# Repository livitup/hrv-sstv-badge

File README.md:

# DEFCON SSTV Badge

An open-source SSTV (Slow Scan Television) badge designed for DEFCON and the broader badgelife community. This badge combines amateur radio, digital imaging, and social interaction into a wearable electronic art piece shaped like a Simpsons-style retro TV with rabbit ear antennas.

## Project Overview

The DEFCON SSTV Badge enables users to:
- **Capture photos** with an integrated 2MP OV2640 camera
- **Encode images** into SSTV format with callsign overlay
- **Transmit images** via VHF/UHF radio using the SA818 transceiver
- **Receive SSTV signals** from other badges and stations
- **Store and browse** images on microSD card
- **Interact socially** through visual radio communication

Perfect for ham radio operators, makers, and anyone interested in digital modes and RF experimentation.

## Features

### Hardware Capabilities
- **RP2350B Dual-Core MCU** - QFN-80, 48 GPIOs, dedicated cores for UI and signal processing
- **SA818 VHF/UHF Transceiver** - 1W output on swappable carrier board (see below)
- **OV2640 2MP Camera** - Parallel DVP interface with 15-20 FPS live viewfinder via PIO (module must have its own on-board clock oscillator)
- **2.4" ILI9341 TFT Display** - 320x240 landscape, SPI interface
- **PCM5102A DAC + RP2350 ADC** - I2S DAC for TX audio, internal ADC for RX audio
- **MicroSD Storage** - Standalone SD socket (J10), shared SPI bus with display
- **2000mAh LiPo Battery** - 8-10 hours operation with USB-C charging
- **2x SAO Connectors** - Standard Shitty Add-On expansion ports
- **26x WS2812B LEDs** - Animated blinky chain across rabbit ears and display border

### Radio Features
- **Dual-Band Support** - VHF (134-174 MHz) and UHF (400-480 MHz) via carrier board swap
- **Multiple SSTV Modes** - Martin, Scottie, Robot modes with auto-detection
- **Automatic Operation** - No manual PTT required
- **Airplane Mode** - Physical slide switch to disable RF
- **SMA Antenna Port** - On carrier board, right-angle connector with antenna pointing up

### User Interface
- **5-Way D-Pad** - Navigation, menu selection, and photo capture (center button doubles as shutter)
- **Airplane Mode Switch** - Slide switch for RF enable/disable
- **PWR LED** - Traditional RGB LED for battery and system status
- **Blinky LEDs** - 26x WS2812B chain with animated TX/RX/idle patterns
- **Customizable Settings** - Callsign, frequency, SSTV mode, and more

## SA818 Carrier Board System

The SA818 transceiver has castellated pads (4.45mm pitch) that are incompatible with user-swappable sockets. Instead of mounting the SA818 directly on the main badge, the design uses a full-width carrier board system.

### How It Works

The carrier board is a separate PCB (full badge width, ~120mm) that overlays the top portion of the main badge. The SA818 module, SMA connector, and antenna are ALL on the carrier board -- the main badge has zero RF traces.

**Mounting:** 4-point connection via 2x 1x8 signal headers (bottom edge) + 2x 1x3 mechanical headers (top corners, grounded for RF shielding).

**Band detection:** Each carrier has an ID resistor (0 ohm for VHF, DNP for UHF) read by the RP2350B on startup. The firmware automatically detects which carrier is installed and configures frequency limits accordingly. No DIP switches or manual configuration needed.

### Carrier Variants

- **SA818-V Carrier** - VHF (134-174 MHz) with matched VHF stubby antenna
- **SA818-U Carrier** - UHF (400-480 MHz) with matched UHF stubby antenna

### Swapping Carriers

1. Power down the badge
2. Unplug the current carrier board from the headers
3. Plug in the replacement carrier (VHF or UHF)
4. Power on -- firmware auto-detects the band and configures itself

Each carrier includes a band-matched stubby antenna, so users do not need to source separate antennas.

### Design Benefits

- Main badge PCB has no RF routing, simplifying layout and potentially enabling 2-layer PCB
- Carrier board has proper 50-ohm microstrip trace from SA818 to SMA
- Ground stitching around RF trace on carrier for shielding
- SA818 is factory-assembled onto carrier (castellated module, not socketable)

## Power System

The SA818 draws up to 1.7A during TX, which would overwhelm a standard 3.3V regulator. The power system separates the radio from the digital rail:

```
LiPo (3.0-4.2V) --+---> TPS63001 (buck-boost) ---> 3.3V Rail (RP2350B, display, camera, etc.)
                   |
                   +---> TPS22919 (load switch) ---> SA818 (3.5-5.5V direct from LiPo)
```

- **TPS63001**: Buck-boost regulator, 3.3V output, handles full LiPo voltage range (3.0-4.2V)
- **TPS22919**: Load switch controls SA818 power (enables airplane mode and sleep)
- **MCP73871**: Battery charging controller with USB-C input
- **LC709203F**: Battery fuel gauge (I2C)

## Amateur Radio License Verification System

To comply with FCC Part 97 regulations, the badge includes a software-based license verification system.

### Operating Modes

- **Receive-Only Mode**: Default for unlicensed users. Can receive and decode SSTV images but cannot transmit.
- **Licensed Mode**: Full TX/RX for verified amateur radio operators.

### Verification Process

During initial setup, users enter their amateur radio callsign. The badge generates a unique unlock code from the callsign and the device's hardware serial number using SHA-256 hashing. This ensures each unlock code is specific to one badge-callsign combination, preventing casual code sharing between devices.

Licensed operators get full transmit capability with automatic callsign overlay on transmitted images (FCC requirement). Unlicensed users can still receive and view SSTV images -- all reception features work normally.

This system encourages proper amateur radio operation. It is not intended as absolute copy protection.

## Project Status

**Current Phase: PCB layout complete — pre-fabrication checks**

| Milestone | Status |
|-----------|--------|
| System architecture and block diagram | Complete |
| Schematic design (all sheets) | Complete, ERC clean |
| KiCad schematic entry | Complete (all sheets) |
| SA818 carrier board PCBs (VHF + UHF) | Complete, including harmonic low-pass filters |
| Bill of materials and sourcing | Complete |
| Main badge PCB layout | Complete (routed) |
| Firmware development | Not started |
| Prototype assembly and testing | Pending PCB fabrication |

## Repository Structure

```
hrv-sstv-badge/
├── CLAUDE.md                       # AI context file (project specs)
├── CMakeLists.txt                  # Build system
├── CONTRIBUTING.md                 # Contribution guidelines
├── LICENSE                         # MIT license
├── README.md                       # This file
├── docs/                           # Documentation
│   ├── block-diagram.png           # System overview diagram
│   ├── electrical-design.md        # Circuit schematics and component specs
│   ├── firmware-architecture.md    # Detailed software design
│   ├── bom.md                      # Bill of materials with costs
│   ├── bom-raw.md                  # Raw BOM data
│   ├── project-status.md           # Design status tracker
│   └── engineers-notebook/         # Design decisions and rationale
├── firmware/                       # RP2350B embedded firmware (not yet started)
├── hardware/                       # KiCad PCB design files
│   ├── main_badge/                 # Main badge KiCad project
│   ├── sa818-v-carrier/            # VHF carrier board KiCad project
│   ├── sa818-u-carrier/            # UHF carrier board KiCad project
│   ├── footprints.pretty/          # Custom KiCad footprints
│   ├── symbols/                    # Custom KiCad symbols
│   ├── pcb-design.md               # PCB layout guidelines
│   └── README.md                   # Hardware design notes
├── mechanical/                     # Badge accessories and mounting
└── src/                            # Source scaffolding
```

## Technical Specifications

| Parameter | Specification |
|-----------|---------------|
| **MCU** | Raspberry Pi RP2350B (QFN-80), Dual ARM Cortex-M33 |
| **Radio** | SA818 VHF/UHF on carrier board, 1W output |
| **Frequency Range** | VHF: 134-174 MHz, UHF: 400-480 MHz |
| **Camera** | OV2640, 2MP, parallel DVP (8-bit), QVGA for SSTV |
| **Display** | 2.4" ILI9341 TFT LCD, 320x240 landscape, SPI |
| **Audio TX** | PCM5102A DAC via I2S |
| **Audio RX** | RP2350B internal ADC with anti-alias filter |
| **Storage** | MicroSD via standalone SD socket J10 (shared SPI bus) |
| **Battery** | 2000mAh LiPo, USB-C charging (MCP73871) |
| **Regulator** | TPS63001 buck-boost, 3.3V output |
| **Operating Time** | 8-10 hours typical use |
| **LEDs** | 26x WS2812B (10x 5050 on the two plug-in ears, 16x 2020 on border) + RGB PWR LED |
| **Expansion** | 2x SAO (Shitty Add-On) connectors |
| **Dimensions** | ~120mm x 120mm body, ~199mm total height with ears and feet |
| **Form Factor** | Retro TV shape with plug-in, replaceable rabbit ear antennas; wearable badge (no enclosure) |

## Software Architecture

The firmware uses a bare-metal dual-core design on the RP2350B for deterministic SSTV timing:

- **Core 0**: User interface, file system, system management, display updates
- **Core 1**: SSTV encoding/decoding, audio DSP, camera control, radio management

PIO state machines handle hardware-timed signals (camera capture, WS2812B data, audio clocking). DMA transfers move data without CPU intervention. No RTOS -- bare metal for microsecond-precision SSTV timing.

### Development Environment
- **Language**: C11 (ISO/IEC 9899:2011)
- **Compiler**: GCC ARM Embedded (arm-none-eabi-gcc)
- **Build System**: CMake with Raspberry Pi Pico SDK
- **Debugger**: OpenOCD + GDB via SWD (Tag-Connect)

## Assembly Model

This badge uses a production kit approach:

- **Factory-assembled**: All SMD components on main badge, SA818 onto carrier boards
- **User-assembled at conference**: Through-hole parts (switches, connectors, pin headers)
- **User-configured**: Plug in VHF or UHF carrier board, insert battery, insert SD card

## Getting Started

### Prerequisites
- **Amateur Radio License** - Required for transmit operation (receive works without)
- **Basic Soldering Skills** - Through-hole soldering for final assembly

### Firmware Installation
1. Download the latest firmware release
2. Connect via USB-C while holding BOOTSEL
3. Copy the UF2 file to the mounted drive
4. Configure callsign, frequency, and SSTV mode

### Build from Source
```bash
mkdir build && cd build
cmake .. -DCMAKE_BUILD_TYPE=Debug
make -j4

# Flash via UF2 bootloader
cp defcon_sstv_badge.uf2 /Volumes/RPI-RP2/

# Or flash via SWD
openocd -f interface/cmsis-dap.cfg -f target/rp2350.cfg
```

## Badgelife Integration

- **SAO Compatibility** - 2x standard Shitty Add-On connectors (I2C + 2 GPIOs each)
- **Badge-to-Badge Communication** - SSTV image exchange over the air
- **Retro TV Aesthetic** - PCB shaped like a classic TV with rabbit ear antennas
- **Animated LEDs** - 26 WS2812B LEDs with TX/RX/idle animations across ears and display border
- **Open Source** - Hardware and software fully open for hacking and modification

## Legal and Compliance

### Amateur Radio Requirements
- Valid amateur radio license required for transmit operation
- Operate only within licensed frequency allocations
- Follow local RF exposure and power limitations
- Respect band plans and operating procedures

### Regulatory
- FCC Part 97 (United States)
- IC RSS (Canada)
- CE marking (Europe)
- Consult local regulations for other countries

### Safety
- RF radiation exposure -- use appropriate antenna and power levels
- LiPo battery safety -- follow proper charging and storage procedures
- ESD precautions during assembly

## Contributing

Contributions from the badgelife and amateur radio communities are welcome.

### How to Contribute
- **Report Issues** - Found a bug? Open a GitHub issue
- **Submit Pull Requests** - Code improvements, documentation fixes
- **Share Ideas** - Feature requests and enhancement suggestions
- **Test Hardware** - Help validate designs and assembly procedures

### Development Areas
- **Hardware**: PCB layout, carrier board design
- **Firmware**: SSTV algorithms, UI, power management
- **Documentation**: Assembly guides, user manuals, tutorials

## License

- **Hardware**: [CERN-OHL-S v2](https://cern-ohl.web.cern.ch/)
- **Software**: [MIT License](LICENSE)
- **Documentation**: [CC BY-SA 4.0](https://creativecommons.org/licenses/by-sa/4.0/)

## Support and Community

- **Documentation** - See the `docs/` directory
- **Issues** - Open a GitHub issue for bugs or questions
- **Discussions** - Use GitHub Discussions for general topics
- **DEFCON** - Hardware Hacking Village and Ham Radio Village

---

**Made for the badgelife and amateur radio communities. See you at DEFCON!**

**73s!**

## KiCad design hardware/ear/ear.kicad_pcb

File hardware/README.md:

# DEFCON SSTV Badge — Hardware Design

This directory contains all KiCad design files for the DEFCON SSTV Badge.

## Directory Structure

```
hardware/
├── main_badge/                    # Main badge KiCad project
│   ├── defcon-sstv-badge.kicad_pro    # Project file
│   ├── defcon-sstv-badge.kicad_sch    # Top-level schematic
│   ├── defcon-sstv-badge.kicad_pcb    # PCB layout (in progress)
│   ├── power.kicad_sch                # Power: TPS63001, TPS22919, MCP73871, LC709203F
│   ├── audio.kicad_sch                # Audio: PCM5102A DAC, TX/RX filters
│   ├── camera-display.kicad_sch       # Display (ILI9341) + Camera (OV2640)
│   ├── mcu.kicad_sch                  # RP2350B, crystal, flash, USB-C
│   ├── switches.kicad_sch             # D-pad, airplane switch, PWR LED, WS2812B chain
│   └── connectors.kicad_sch           # SAO×2, carrier headers, SD card, Tag-Connect
├── sa818-v-carrier/               # VHF carrier board (134-174 MHz)
│   ├── sa818-v-carrier.kicad_pro
│   ├── sa818-v-carrier.kicad_sch
│   └── sa818-v-carrier.kicad_pcb      # PCB layout complete
├── sa818-u-carrier/               # UHF carrier board (400-480 MHz)
│   ├── sa818-u-carrier.kicad_pro
│   ├── sa818-u-carrier.kicad_sch
│   └── sa818-u-carrier.kicad_pcb      # PCB layout complete
├── ear/                           # Plug-in rabbit ear LED board (one design, used twice)
│   ├── ear.kicad_pro
│   ├── ear.kicad_sch
│   └── ear.kicad_pcb                  # PCB layout complete
├── symbols/                       # Custom KiCad symbol libraries
├── footprints.pretty/             # Custom KiCad footprint libraries
├── fp-lib-table                   # Footprint library table
├── sym-lib-table                  # Symbol library table
├── pcb-design.md                  # PCB outline, dimensions, and layout zones
└── README.md                      # This file
```

## Design Overview

### Main Badge
- **PCB shape**: Simpsons-style retro TV with stubby feet; the rabbit ear antennas are two plug-in boards (`ear/`)
- **Body dimensions**: 120mm × 120mm
- **Total height**: ~199mm with ears plugged in (main board alone 139mm)
- **Layer count**: Targeting 4-layer (signal/ground/power/signal)
- **Thickness**: 1.6mm standard FR4
- **Soldermask**: Purple with white silkscreen (Simpsons TV aesthetic)

### Rabbit Ears
- **One board, used twice**: 15 × 95.5mm, 2-layer, five WS2812B LEDs and a 2×3 header
- Plugs into sockets J24/J25 on the back of the main badge; replaceable
- See `docs/engineers-notebook/plug-in-ears.md`

### Carrier Boards
- **Size**: Full badge width (~120mm), overlays top of main badge
- **Purpose**: SA818 module + SMA connector + antenna — all RF on carrier, none on main badge
- **Variants**: VHF (SA818-V) and UHF (SA818-U), identical PCB with different module population
- **PCB layout**: Complete for both variants

### Key Design Decisions
- **No RF on main badge** — all RF routing is on the carrier board
- **Carrier is front-mounted** — overlays the top portion of the main badge, top edges flush
- **4-point mounting** — 2× 1×8 signal headers + 2× 1×3 mechanical headers (GND for RF shielding)
- **Band auto-detect** — carrier ID resistor (0Ω to GND = VHF, 10kΩ pull-up = UHF) read by firmware on startup

## KiCad Version

This project uses **KiCad 9**. Custom symbols and footprints are included in the repository.

## Schematic Status

All schematic sheets are complete and ERC clean:
- Power, Audio, Display/Camera, MCU, Switches, Connectors (main badge)
- SA818-V Carrier, SA818-U Carrier

## PCB Layout Status

- **Carrier boards**: Complete (VHF and UHF), including the harmonic low-pass filter; headers mount on the back
- **Main badge**: Routing complete

## Related Documentation

- [PCB Design](pcb-design.md) — Board outline, dimensions, component placement zones
- [Electrical Design](../docs/electrical-design.md) — Circuit schematics and component specs
- [BOM](../docs/bom.md) — Bill of materials with costs and sourcing
- [Project Status](../docs/project-status.md) — Design and implementation tracker

---

*73 de HRV*

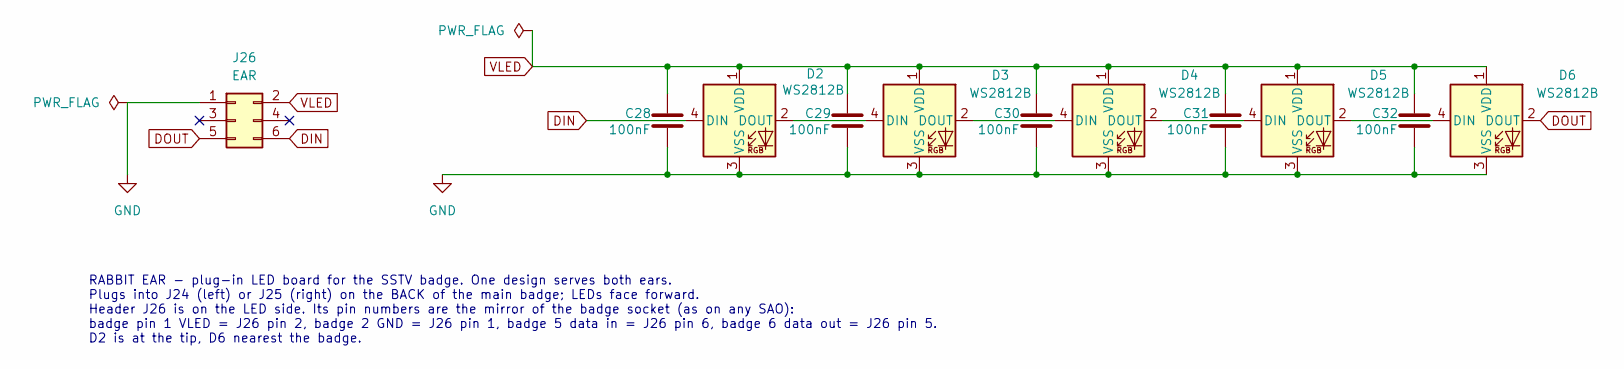
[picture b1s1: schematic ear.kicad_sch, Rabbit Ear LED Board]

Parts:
C28, C29, C30, C31, C32: 100nF; C_0402_1005Metric
D2, D3, D4, D5, D6: WS2812B; LED_WS2812B_PLCC4_5.0x5.0mm_P3.2mm
J26: EAR; PinHeader_2x03_P2.54mm_Vertical

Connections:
DIN: D2.4 (DIN), J26.6
DOUT: D6.2 (DOUT), J26.5
GND: C28.2, C29.2, C30.2, C31.2, C32.2, D2.3 (VSS), D3.3 (VSS), D4.3 (VSS), D5.3 (VSS), D6.3 (VSS), J26.1
unnamed: D2.2 (DOUT), D3.4 (DIN)
unnamed: D3.2 (DOUT), D4.4 (DIN)
unnamed: D4.2 (DOUT), D5.4 (DIN)
unnamed: D5.2 (DOUT), D6.4 (DIN)
VLED: C28.1, C29.1, C30.1, C31.1, C32.1, D2.1 (VDD), D3.1 (VDD), D4.1 (VDD), D5.1 (VDD), D6.1 (VDD), J26.2

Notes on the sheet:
RABBIT EAR - plug-in LED board for the SSTV badge. One design serves both ears. Plugs into J24 (left) or J25 (right) on the BACK of the main badge; LEDs face forward. Header J26 is on the LED side. Its pin numbers are the mirror of the badge socket (as on any SAO): badge pin 1 VLED = J26 pin 2, bad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

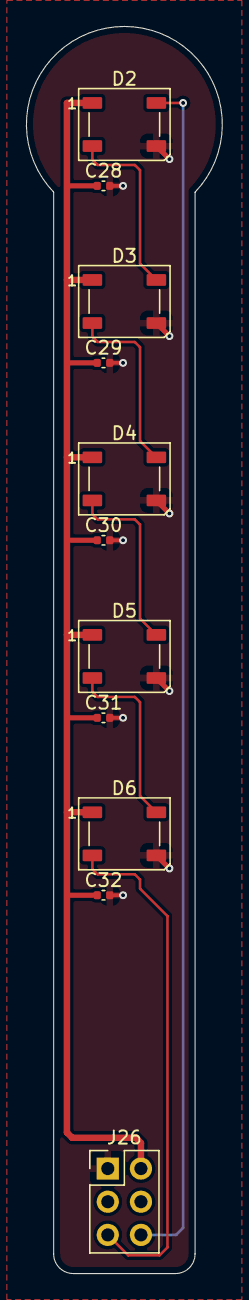
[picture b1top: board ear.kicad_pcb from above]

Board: 2 copper layers, 15.0 x 95.5 mm, 11 parts (0 on the bottom side), 8 nets.

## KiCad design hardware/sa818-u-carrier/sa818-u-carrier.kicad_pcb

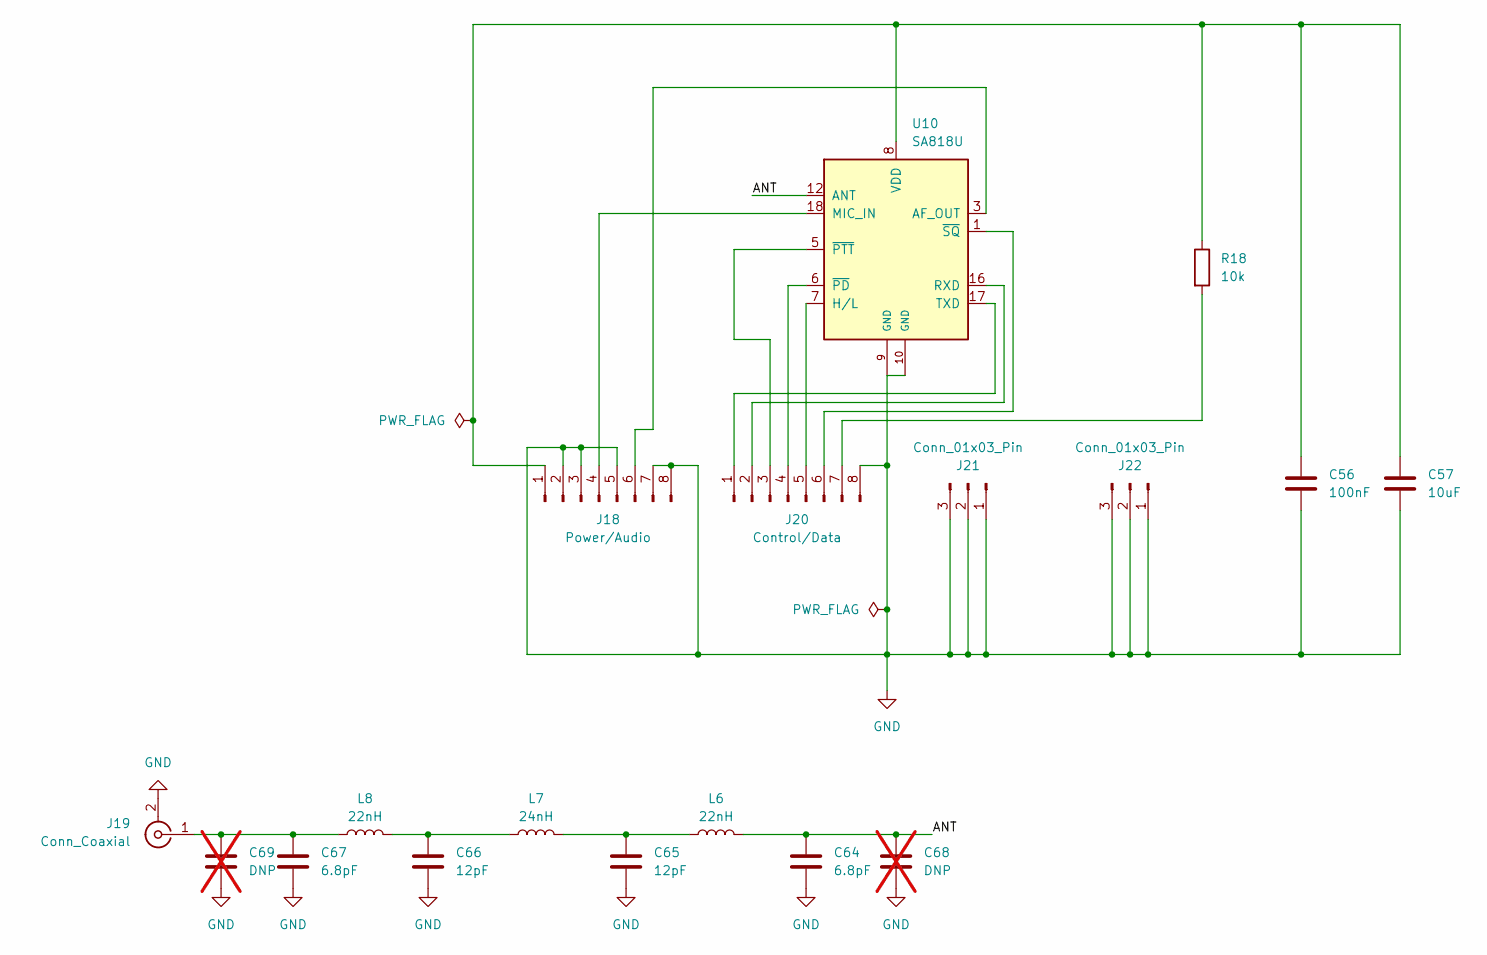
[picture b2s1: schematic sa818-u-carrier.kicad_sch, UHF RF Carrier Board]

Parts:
C56: 100nF; C_0402_1005Metric
C57: 10uF; C_0603_1608Metric
C64, C67: 6.8pF; C_0402_1005Metric
C65, C66: 12pF; C_0402_1005Metric
C68, C69: DNP; C_0402_1005Metric; not fitted
J18: Power/Audio; PinHeader_1x08_P2.54mm_Vertical
J19: Conn_Coaxial; SMA_Amphenol_132289_EdgeMount
J20: Control/Data; PinHeader_1x08_P2.54mm_Vertical
J21, J22: Conn_01x03_Pin; PinHeader_1x03_P2.54mm_Vertical
L6, L8: 22nH; L_0603HP
L7: 24nH; L_0603HP
R18: 10k; R_0402_1005Metric
U10: SA818U; VHF_UHF_Module_generic

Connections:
/ANT: C64.2, C68.1, L6.2, U10.12 (ANT)
GND: C56.2, C57.2, C64.1, C65.1, C66.2, C67.2, C68.2, C69.2, J18.2, J18.3, J18.5, J18.7, J18.8, J19.2 (Ext), J20.8, J21.1, J21.2, J21.3, J22.1, J22.2, J22.3, U10.9 (GND), U10.10 (GND)
unnamed: C65.2, L6.1, L7.2
unnamed: C66.1, L7.1, L8.2
unnamed: C56.1, C57.1, J18.1, R18.1, U10.8 (VDD)
unnamed: J18.4, U10.18 (MIC_IN)
unnamed: J18.6, U10.3 (AF_OUT)
unnamed: C67.1, C69.1, J19.1 (In), L8.1
unnamed: J20.1, U10.17 (TXD)
unnamed: J20.2, U10.16 (RXD)
unnamed: J20.3, U10.5 (~PTT)
unnamed: J20.4, U10.6 (~PD)
unnamed: J20.5, U10.7 (H/L)
unnamed: J20.6, U10.1 (~SQ)
unnamed: J20.7, R18.2

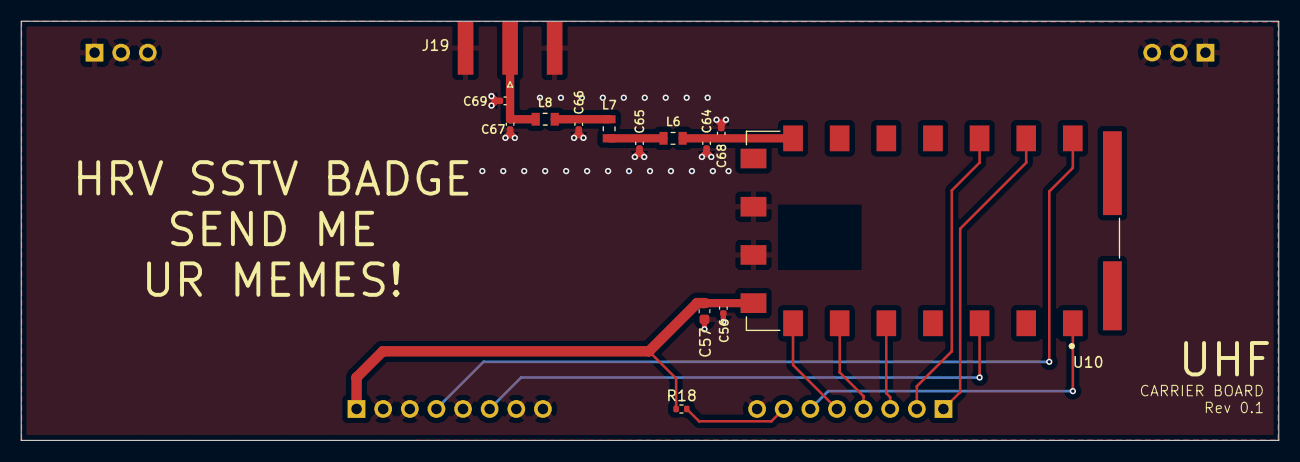
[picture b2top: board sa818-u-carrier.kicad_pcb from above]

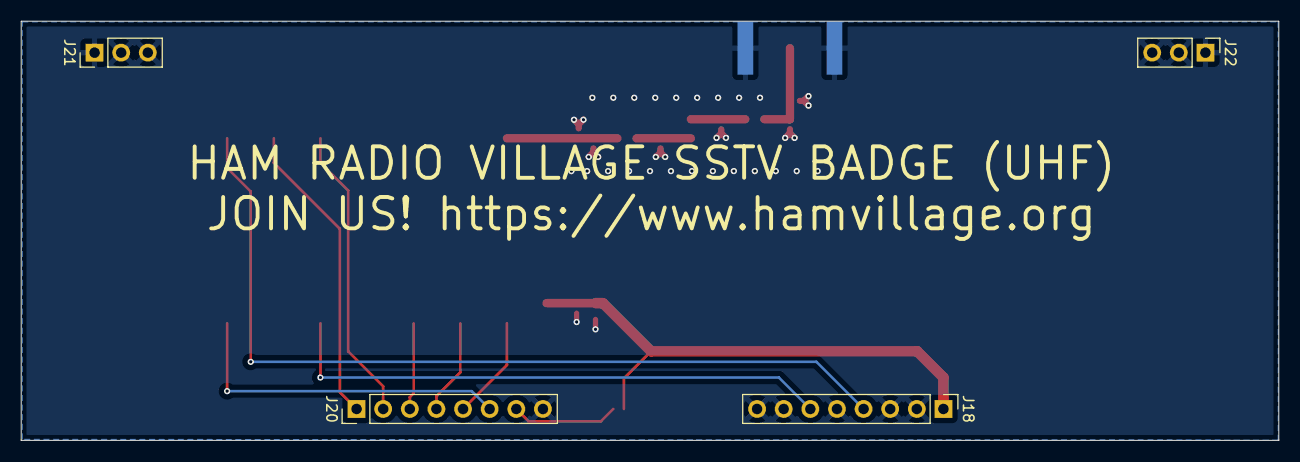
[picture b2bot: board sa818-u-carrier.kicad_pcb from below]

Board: 2 copper layers, 120.0 x 40.0 mm, 18 parts (4 on the bottom side), 15 nets.

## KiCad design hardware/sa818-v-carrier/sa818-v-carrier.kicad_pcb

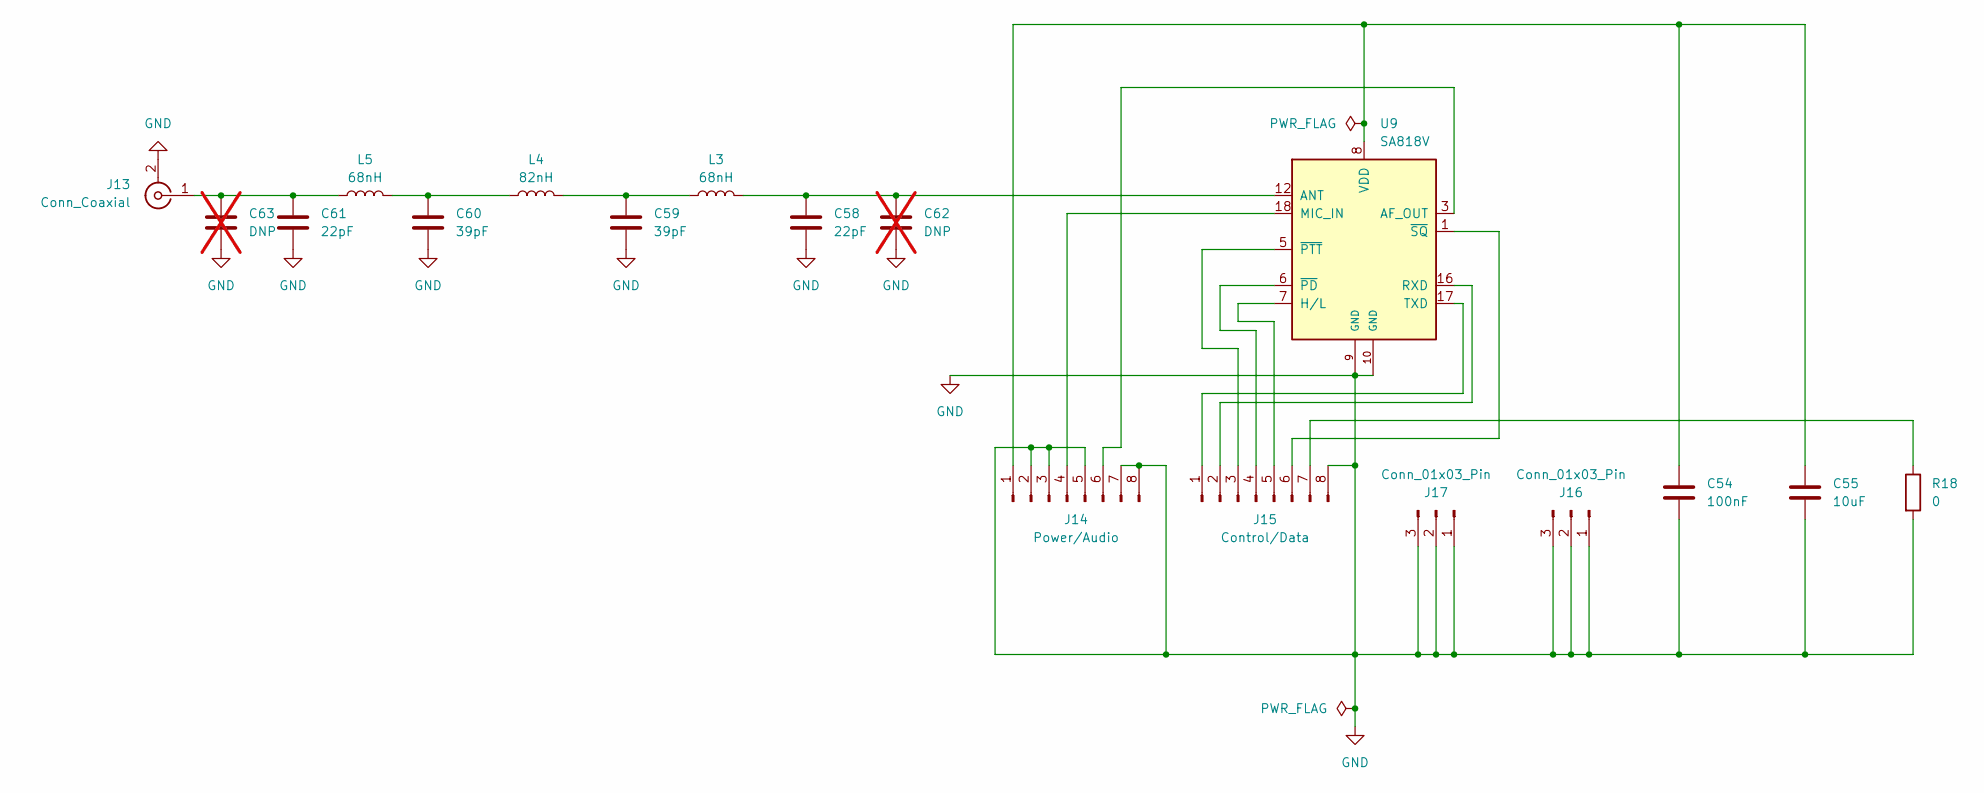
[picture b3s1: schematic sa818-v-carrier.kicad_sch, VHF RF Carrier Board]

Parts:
C54: 100nF; C_0402_1005Metric
C55: 10uF; C_0603_1608Metric
C58, C61: 22pF; C_0402_1005Metric
C59, C60: 39pF; C_0402_1005Metric
C62, C63: DNP; C_0402_1005Metric; not fitted
J13: Conn_Coaxial; SMA_Amphenol_132289_EdgeMount
J14: Power/Audio; PinHeader_1x08_P2.54mm_Vertical
J15: Control/Data; PinHeader_1x08_P2.54mm_Vertical
J16, J17: Conn_01x03_Pin; PinHeader_1x03_P2.54mm_Vertical
L3, L5: 68nH; L_0603HP
L4: 82nH; L_0603HP
R18: 0; R_0402_1005Metric
U9: SA818V; VHF_UHF_Module_generic

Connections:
GND: C54.2, C55.2, C58.1, C59.1, C60.2, C61.2, C62.2, C63.2, J13.2 (Ext), J14.2, J14.3, J14.5, J14.7, J14.8, J15.8, J16.1, J16.2, J16.3, J17.1, J17.2, J17.3, R18.2, U9.9 (GND), U9.10 (GND)
unnamed: C59.2, L3.1, L4.2
unnamed: C60.1, L4.1, L5.2
unnamed: C61.1, C63.1, J13.1 (In), L5.1
unnamed: C54.1, C55.1, J14.1, U9.8 (VDD)
unnamed: J14.4, U9.18 (MIC_IN)
unnamed: J14.6, U9.3 (AF_OUT)
unnamed: J15.1, U9.17 (TXD)
unnamed: J15.2, U9.16 (RXD)
unnamed: J15.3, U9.5 (~PTT)
unnamed: J15.4, U9.6 (~PD)
unnamed: J15.5, U9.7 (H/L)
unnamed: J15.6, U9.1 (~SQ)
unnamed: J15.7, R18.1
unnamed: C58.2, C62.1, L3.2, U9.12 (ANT)

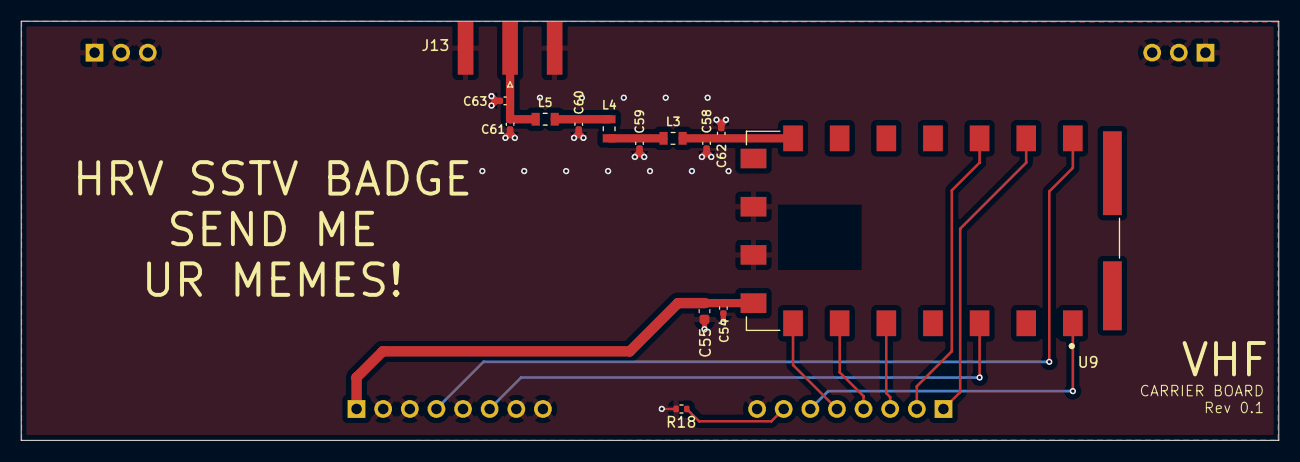
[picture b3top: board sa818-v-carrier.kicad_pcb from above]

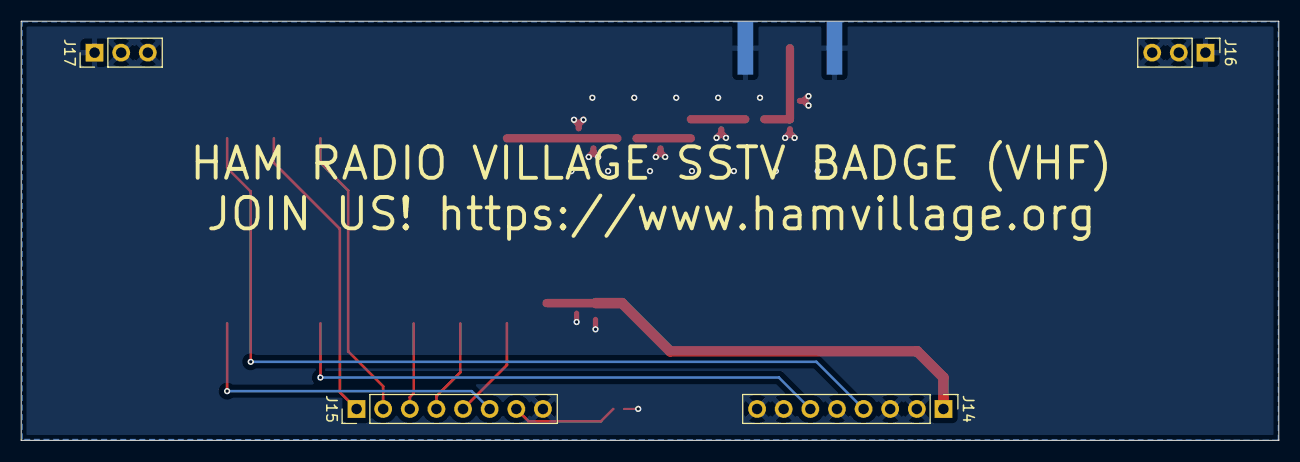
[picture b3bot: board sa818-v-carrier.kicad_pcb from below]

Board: 2 copper layers, 120.0 x 40.0 mm, 18 parts (4 on the bottom side), 15 nets.

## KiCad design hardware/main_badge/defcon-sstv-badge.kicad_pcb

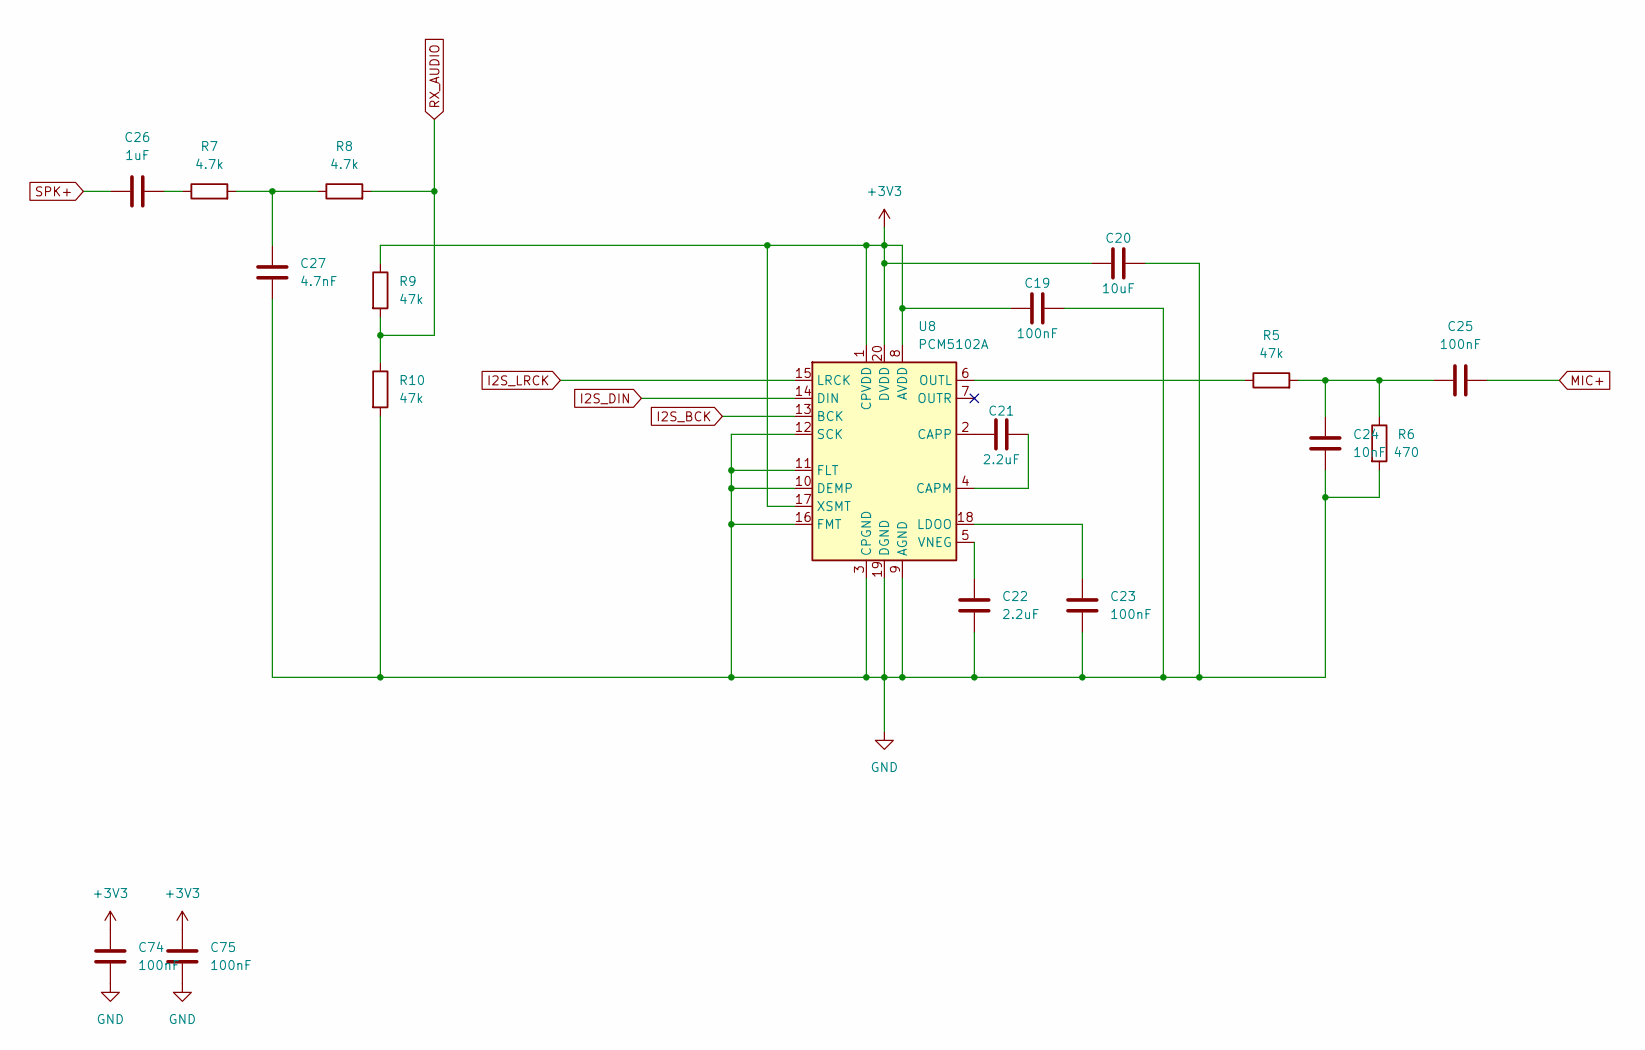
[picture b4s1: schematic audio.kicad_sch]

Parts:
C19, C23, C25: 100nF; C_0603_1608Metric
C20: 10uF; C_0805_2012Metric
C21, C22: 2.2uF; C_0603_1608Metric
C24: 10nF; C_0603_1608Metric
C26: 1uF; C_0603_1608Metric
C27: 4.7nF; C_0603_1608Metric
C74, C75: 100nF; C_0402_1005Metric
R5, R9, R10: 47k; R_0603_1608Metric
R6: 470; R_0603_1608Metric
R7, R8: 4.7k; R_0603_1608Metric
U8: PCM5102A; TSSOP-20_4.4x6.5mm_P0.65mm

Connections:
+3V3: C19.1, C20.1, C74.1, C75.1, R9.1, U8.1 (CPVDD), U8.8 (AVDD), U8.17 (XSMT), U8.20 (DVDD); also elsewhere on the board
I2S_BCK: U8.13 (BCK); also elsewhere on the board
I2S_DIN: U8.14 (DIN); also elsewhere on the board
I2S_LRCK: U8.15 (LRCK); also elsewhere on the board
MIC+: C25.2; also elsewhere on the board
unnamed: C24.1, C25.1, R5.2, R6.1
unnamed: C26.2, R7.1
unnamed: C27.1, R7.2, R8.1
unnamed: C21.2, U8.4 (CAPM)
unnamed: C21.1, U8.2 (CAPP)
unnamed: C23.1, U8.18 (LDOO)
unnamed: R5.1, U8.6 (OUTL)
unnamed: C22.1, U8.5 (VNEG)
RX_AUDIO: R8.2, R9.2, R10.1; also elsewhere on the board
SPK+: C26.1; also elsewhere on the board

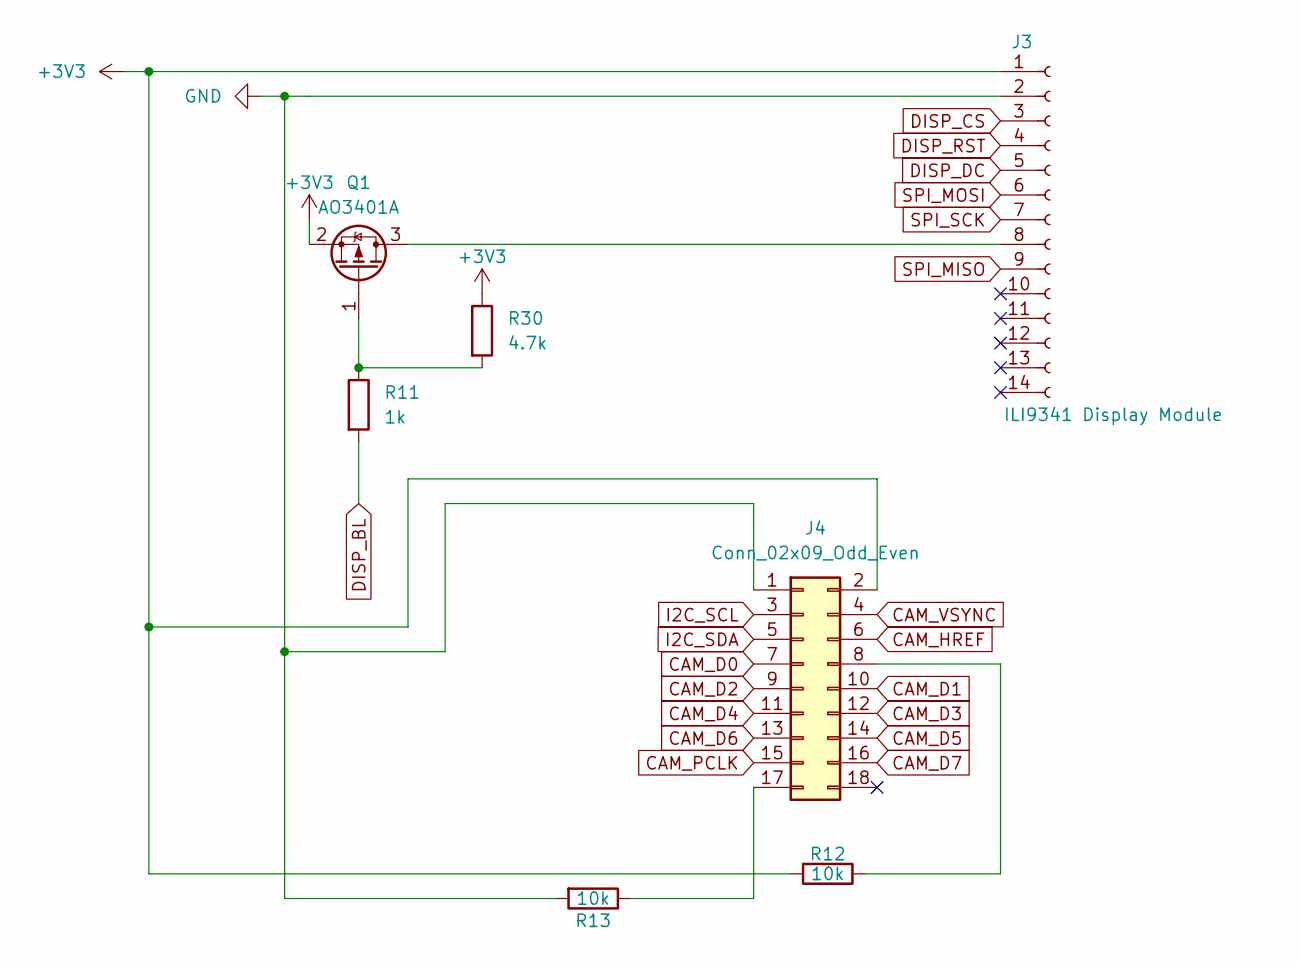
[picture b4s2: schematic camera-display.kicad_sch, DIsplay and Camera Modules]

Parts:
J3: ILI9341 Display Module; PinSocket_1x14_P2.54mm_Vertical
J4: Conn_02x09_Odd_Even; PinSocket_2x09_P2.54mm_Vertical
Q1: AO3401A; SOT-23
R11: 1k; R_0603_1608Metric
R12, R13: 10k; R_0603_1608Metric
R30: 4.7k; R_0402_1005Metric

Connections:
+3V3: J3.1, J4.2, Q1.2 (S), R12.2, R30.1; also elsewhere on the board
CAM_D0: J4.7; also elsewhere on the board
CAM_D1: J4.10; also elsewhere on the board
CAM_D2: J4.9; also elsewhere on the board
CAM_D3: J4.12; also elsewhere on the board
CAM_D4: J4.11; also elsewhere on the board
CAM_D5: J4.14; also elsewhere on the board
CAM_D6: J4.13; also elsewhere on the board
CAM_D7: J4.16; also elsewhere on the board
CAM_HREF: J4.6; also elsewhere on the board
CAM_PCLK: J4.15; also elsewhere on the board
CAM_VSYNC: J4.4; also elsewhere on the board
DISP_BL: R11.2; also elsewhere on the board
DISP_CS: J3.3; also elsewhere on the board
DISP_DC: J3.5; also elsewhere on the board
DISP_RST: J3.4; also elsewhere on the board
I2C_SCL: J4.3; also elsewhere on the board
I2C_SDA: J4.5; also elsewhere on the board
unnamed: J3.8, Q1.3 (D)
unnamed: J4.8, R12.1
unnamed: J4.17, R13.1
unnamed: Q1.1 (G), R11.1, R30.2
SPI_MISO: J3.9; also elsewhere on the board
SPI_MOSI: J3.6; also elsewhere on the board
SPI_SCK: J3.7; also elsewhere on the board

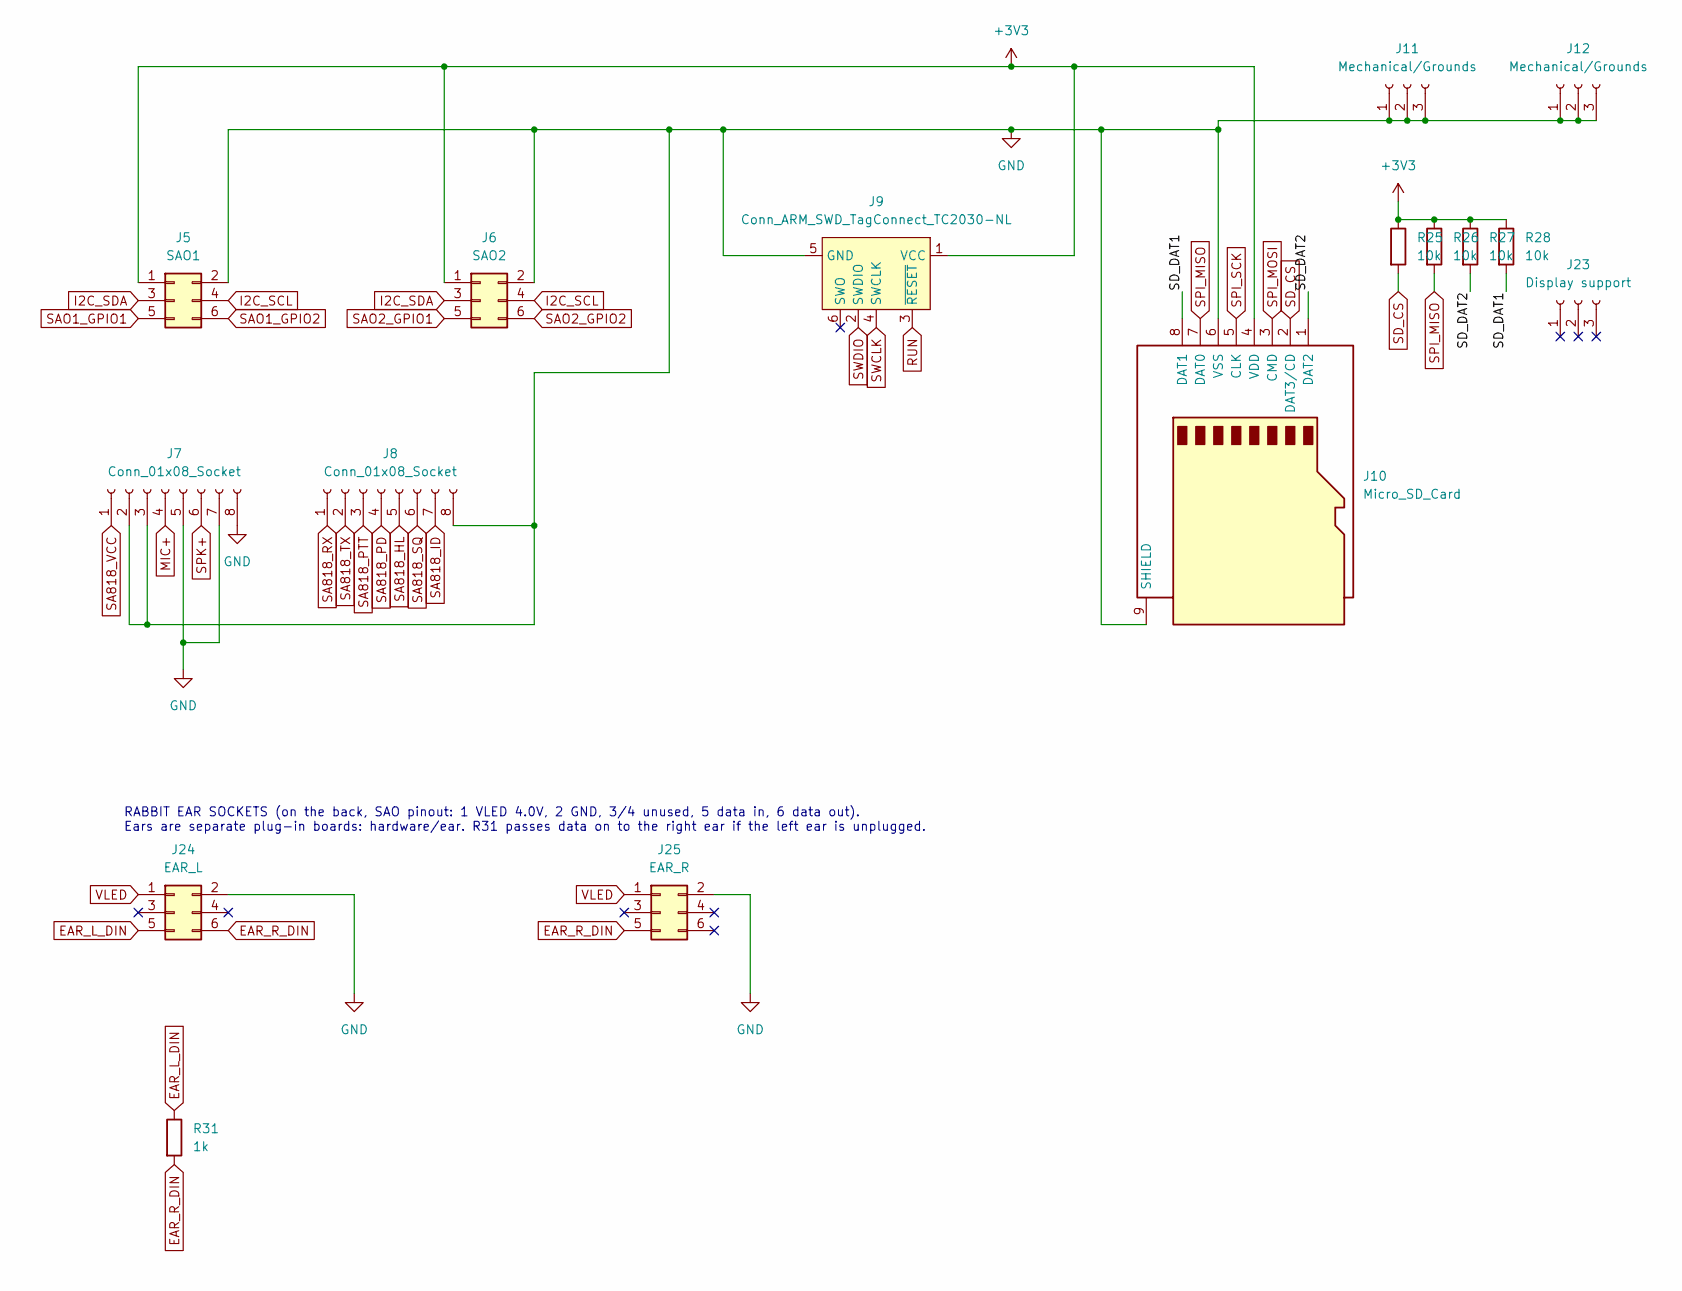
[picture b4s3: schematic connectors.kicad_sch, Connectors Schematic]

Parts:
J5: SAO1; PinHeader_2x03_P2.54mm_Vertical
J6: SAO2; PinHeader_2x03_P2.54mm_Vertical
J7, J8: Conn_01x08_Socket; PinSocket_1x08_P2.54mm_Vertical
J9: Conn_ARM_SWD_TagConnect_TC2030-NL; Tag-Connect_TC2030-IDC-NL_2x03_P1.27mm_Vertical
J10: Micro_SD_Card; microSD_HC_Molex_104031-0811
J11, J12: Mechanical/Grounds; PinSocket_1x03_P2.54mm_Vertical
J23: Display support; PinSocket_1x03_P2.54mm_Vertical
J24: EAR_L; PinHeader_2x03_P2.54mm_Vertical
J25: EAR_R; PinHeader_2x03_P2.54mm_Vertical
R25, R26, R27, R28: 10k; R_0402_1005Metric
R31: 1k; R_0402_1005Metric

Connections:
+3V3: J5.1, J6.1, J9.1 (VCC), J10.4 (VDD), R25.1, R26.1, R27.1, R28.1; also elsewhere on the board
/Connectors/SD_DAT1: J10.8 (DAT1), R28.2
/Connectors/SD_DAT2: J10.1 (DAT2), R27.2
EAR_L_DIN: J24.5, R31.1; also elsewhere on the board
EAR_R_DIN: J24.6, J25.5, R31.2
I2C_SCL: J5.4, J6.4; also elsewhere on the board
I2C_SDA: J5.3, J6.3; also elsewhere on the board
MIC+: J7.4; also elsewhere on the board
RUN: J9.3 (~RESET); also elsewhere on the board
SA818_HL: J8.5; also elsewhere on the board
SA818_ID: J8.7; also elsewhere on the board
SA818_PD: J8.4; also elsewhere on the board
SA818_PTT: J8.3; also elsewhere on the board
SA818_RX: J8.1; also elsewhere on the board
SA818_SQ: J8.6; also elsewhere on the board
SA818_TX: J8.2; also elsewhere on the board
SA818_VCC: J7.1; also elsewhere on the board
SAO1_GPIO1: J5.5; also elsewhere on the board
SAO1_GPIO2: J5.6; also elsewhere on the board
SAO2_GPIO1: J6.5; also elsewhere on the board
SAO2_GPIO2: J6.6; also elsewhere on the board
SD_CS: J10.2 (DAT3/CD), R25.2; also elsewhere on the board
SPI_MISO: J10.7 (DAT0), R26.2; also elsewhere on the board
SPI_MOSI: J10.3 (CMD); also elsewhere on the board
SPI_SCK: J10.5 (CLK); also elsewhere on the board
SPK+: J7.6; also elsewhere on the board
SWCLK: J9.4 (SWCLK); also elsewhere on the board
SWDIO: J9.2 (SWDIO); also elsewhere on the board
VLED: J24.1, J25.1; also elsewhere on the board

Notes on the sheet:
RABBIT EAR SOCKETS (on the back, SAO pinout: 1 VLED 4.0V, 2 GND, 3/4 unused, 5 data in, 6 data out). Ears are separate plug-in boards: hardware/ear. R31 passes data on to the right ear if the left ear is unplugged.
